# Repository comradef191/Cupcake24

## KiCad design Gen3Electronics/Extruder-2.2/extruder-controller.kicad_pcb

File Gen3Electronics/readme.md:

# About
The electronics within the final Cupcake24 build will be a modernised variant of the original Gen3 electronics, with the following changes made from the original files:

- PCB & Schematics ported to KiCAD 8.0
  - Reorganisation of Schematic to fit into one small page
  - Symbol locations adjusted to make values easier to read
  - Where possible, Schematic symbols swapped for KiCAD equivalents
  - Where possible, PCB footprints swapped for KiCAD equivalents
- PCB outline re-drawn and rounded-off
- PCB modified to run ground through the groundplane, rather than individual traces
- All traces, text, vias ect adjusted to be entirely metric (I.E: 0.3048mm traces (12mill) changed to 0.3mm traces)
- Silkscreen entirely overhauled, with information more clearly marked, text relocated & re-sized for improved readability, and information about Cupcake24 in an out-of-sight place (Generally, the rear of the PCB, or under a large component such as the SD reader)
- Some minor fixes to some traces not being run entirely in straight lines

# Electronics Status:

**RepRap Motherboard v1.2**
- [x] Converted to modern Eagle
- [x] Files Ported to KiCAD 8.0
- [x] Schematic modernised & cleaned-up
- [ ] PCB Modernised & cleaned-up
- [ ] Component sources designated; BoM Complete
- [ ] PCB Ordered
- [ ] PCB Assembled & Tested
- Comment: PCB mostly complete, some cleanup and tweaks to be done.

**Stepper Motor Driver v2.3**
- [x] Converted to modern Eagle
- [x] Files Ported to KiCAD 8.0
- [x] Schematic modernised & cleaned-up
- [x] PCB Modernised & cleaned-up
- [x] Component sources designated; BoM Complete
- [ ] PCB Ordered
- [ ] PCB Assembled & Tested

**Extruder Controller v2.2**
- [x] Converted to modern Eagle
- [x] Files Ported to KiCAD 8.0
- [ ] Schematic modernised & cleaned-up
- [ ] PCB Modernised & cleaned-up
- [ ] Component sources designated; BoM Complete
- [ ] PCB Ordered
- [ ] PCB Assembled & Tested

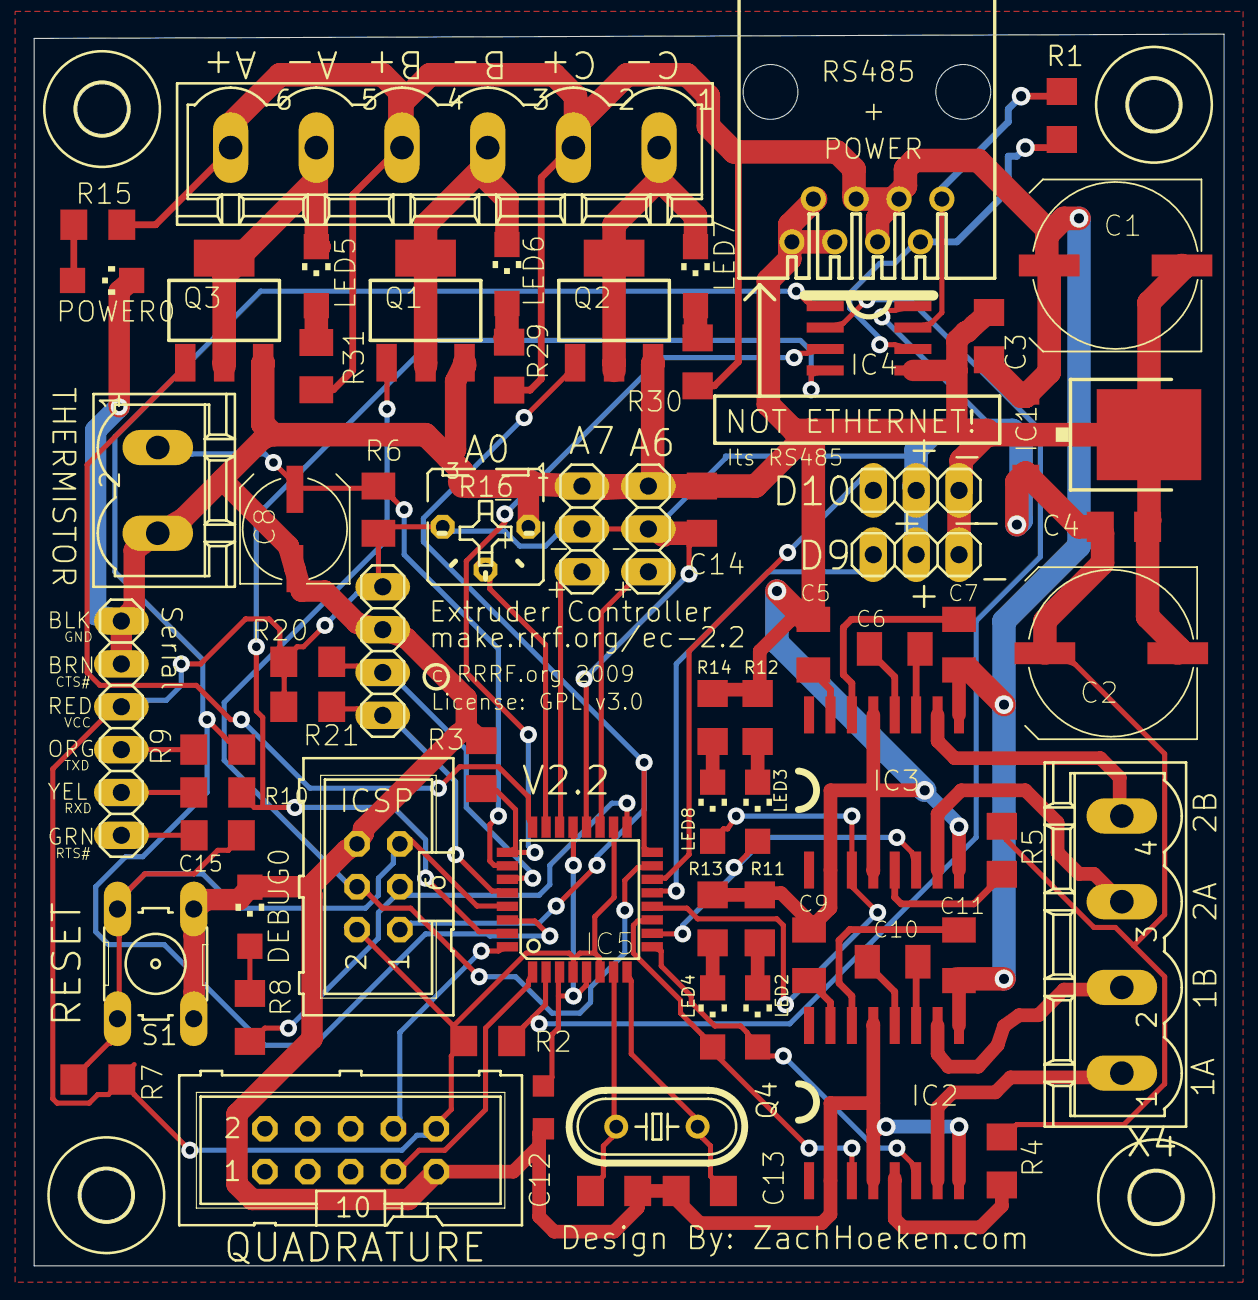
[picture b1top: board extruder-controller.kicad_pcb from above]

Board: 2 copper layers, 70.5 x 73.0 mm, 71 parts (0 on the bottom side), 61 nets.

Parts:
C1, C2: 100uF; UD-10X10_NICHICON
C3, C4, C14, C15: 100nF; C1206
C5, C9: .22uF; C1206K
C6, C7, C10, C11: 100nF; C1206K
C8: 10uF; UD-6,3X5,8_NICHICON
C12, C13: 16pf; C1206
DEBUG0: CHIPLED_1206
H1, H2, H3, H4: MOUNT-HOLE3.0; 3,0
IC1: 7805DT; TO252
IC2, IC3: A3949; SO16W
IC4: SN75176ASOIC; SO08
IC5: ATMEGA168; TQFP32-08
J1: 520426-4
JP2, JP3, JP6, JP7: 1X03
JP4: 1X04
JP5: 1X06
LED2: 1; CHIPLED_1206
LED3: 2; CHIPLED_1206
LED4, LED5, LED6, LED7, LED8: CHIPLED_1206
POWER0: CHIPLED_1206
Q1, Q2, Q3: NIF5002; SOT223
Q4: 16MHZ; HC49_S
R1: 180; R1206
R2, R3: 4.7k; R1206
R4, R5, R7: 10K; R1206
R6: 4.7K; M1206
R8, R9, R10, R11, R12, R13, R14, R15, R29, R30: 1K; R1206
R16: B25P
R20, R21: 4.7K; R1206
R31: 1K; M1206
S1: B3F-10XX
SV1: ML6
SV2: ML10
X1: MSTBV6
X3: MSTBV2
X4: MSTBV4

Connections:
+12V: C1.+, C3.1, C7.2, C11.2, IC1.1, IC2.9, IC3.9, J1.3, J1.4, J1.5, R15.2, R29.2, R30.2, R31.2, X1.2, X1.4, X1.6
A0: IC5.23, R16.S
A1: IC5.24, Q3.1
A2: IC4.3, IC5.25, R3.1
A3: C8.+, IC5.26, R6.1, X3.1
A6: IC5.19, JP6.3
A7: IC5.22, JP7.3
D2: IC5.32, SV2.8
D3: IC5.1, SV2.7
D4: IC4.2, IC5.2, R2.1
D5: IC2.6, IC5.9, LED2.A
D6: IC3.6, IC5.10, LED3.A
D7: IC2.3, IC5.11, LED4.A
D8: IC3.3, IC5.12, LED8.A
D9: IC5.13, JP3.3
D10: IC5.14, JP2.3
D11: IC5.15, Q1.1, SV1.4
D12: IC5.16, Q2.1, SV1.1
D13: IC5.17, R8.2, SV1.3
GND: C1.-, C2.-, C3.2, C4.2, C5.1, C8.-, C9.1, C12.1, C13.1, C14.1, DEBUG0.C, IC1.3, IC2.2, IC2.4, IC2.8, IC2.13, IC3.2, IC3.4, IC3.8, IC3.13, IC4.5, J1.6, J1.7, J1.8, JP2.1, JP3.1, JP4.2, JP5.1, JP5.2, JP6.1, JP7.1, POWER0.C, Q1.3, Q2.3, Q3.3, R3.2, R11.2, R12.2, R13.1, R14.1, R16.A, S1.3, S1.4, SV1.6, SV2.9, X3.2
GNDA: IC5.3, IC5.5, IC5.21
unnamed: IC4.7, J1.1, R1.2
unnamed: IC4.6, J1.2, R1.1
unnamed: C9.2, IC2.15
unnamed: IC2.7, X4.1
unnamed: IC2.10, X4.2
unnamed: C10.2, IC2.12
unnamed: C10.1, IC2.11
unnamed: DEBUG0.A, R8.1
unnamed: C11.1, IC2.14
unnamed: IC3.7, X4.3
unnamed: C5.2, IC3.15
unnamed: IC2.5, R4.2
unnamed: C6.2, IC3.12
unnamed: C6.1, IC3.11
unnamed: C7.1, IC3.14
unnamed: IC3.5, R5.2
unnamed: IC3.10, X4.4
unnamed: LED2.C, R11.1
unnamed: LED3.C, R12.1
unnamed: C14.2, IC5.20
unnamed: JP5.5, R10.1
unnamed: JP5.4, R9.1
unnamed: LED4.C, R13.2
unnamed: LED8.C, R14.2
unnamed: POWER0.A, R15.1
unnamed: C12.2, IC5.7, Q4.2
unnamed: C13.2, IC5.8, Q4.1
unnamed: LED7.C, Q2.2, Q2.4, X1.1
unnamed: LED6.C, Q1.2, Q1.4, X1.3
unnamed: LED5.C, Q3.2, Q3.4, X1.5
unnamed: LED5.A, R31.1
unnamed: LED6.A, R29.1
unnamed: LED7.A, R30.1
RESET: C15.1, IC5.29, R7.1, S1.1, S1.2, SV1.5
RTS#: C15.2, JP5.6
RX: IC4.1, IC5.30, R9.2
SCL: IC5.28, JP4.4, R21.1
SDA: IC5.27, JP4.3, R20.1
TX: IC4.4, IC5.31, R10.2
VCC: C2.+, C4.1, IC1.2, IC4.8, IC5.4, IC5.6, IC5.18, JP2.2, JP3.2, JP4.1, JP5.3, JP6.2, JP7.2, R2.2, R4.1, R5.1, R6.2, R7.2, R16.E, R20.2, R21.2, SV1.2, SV2.10

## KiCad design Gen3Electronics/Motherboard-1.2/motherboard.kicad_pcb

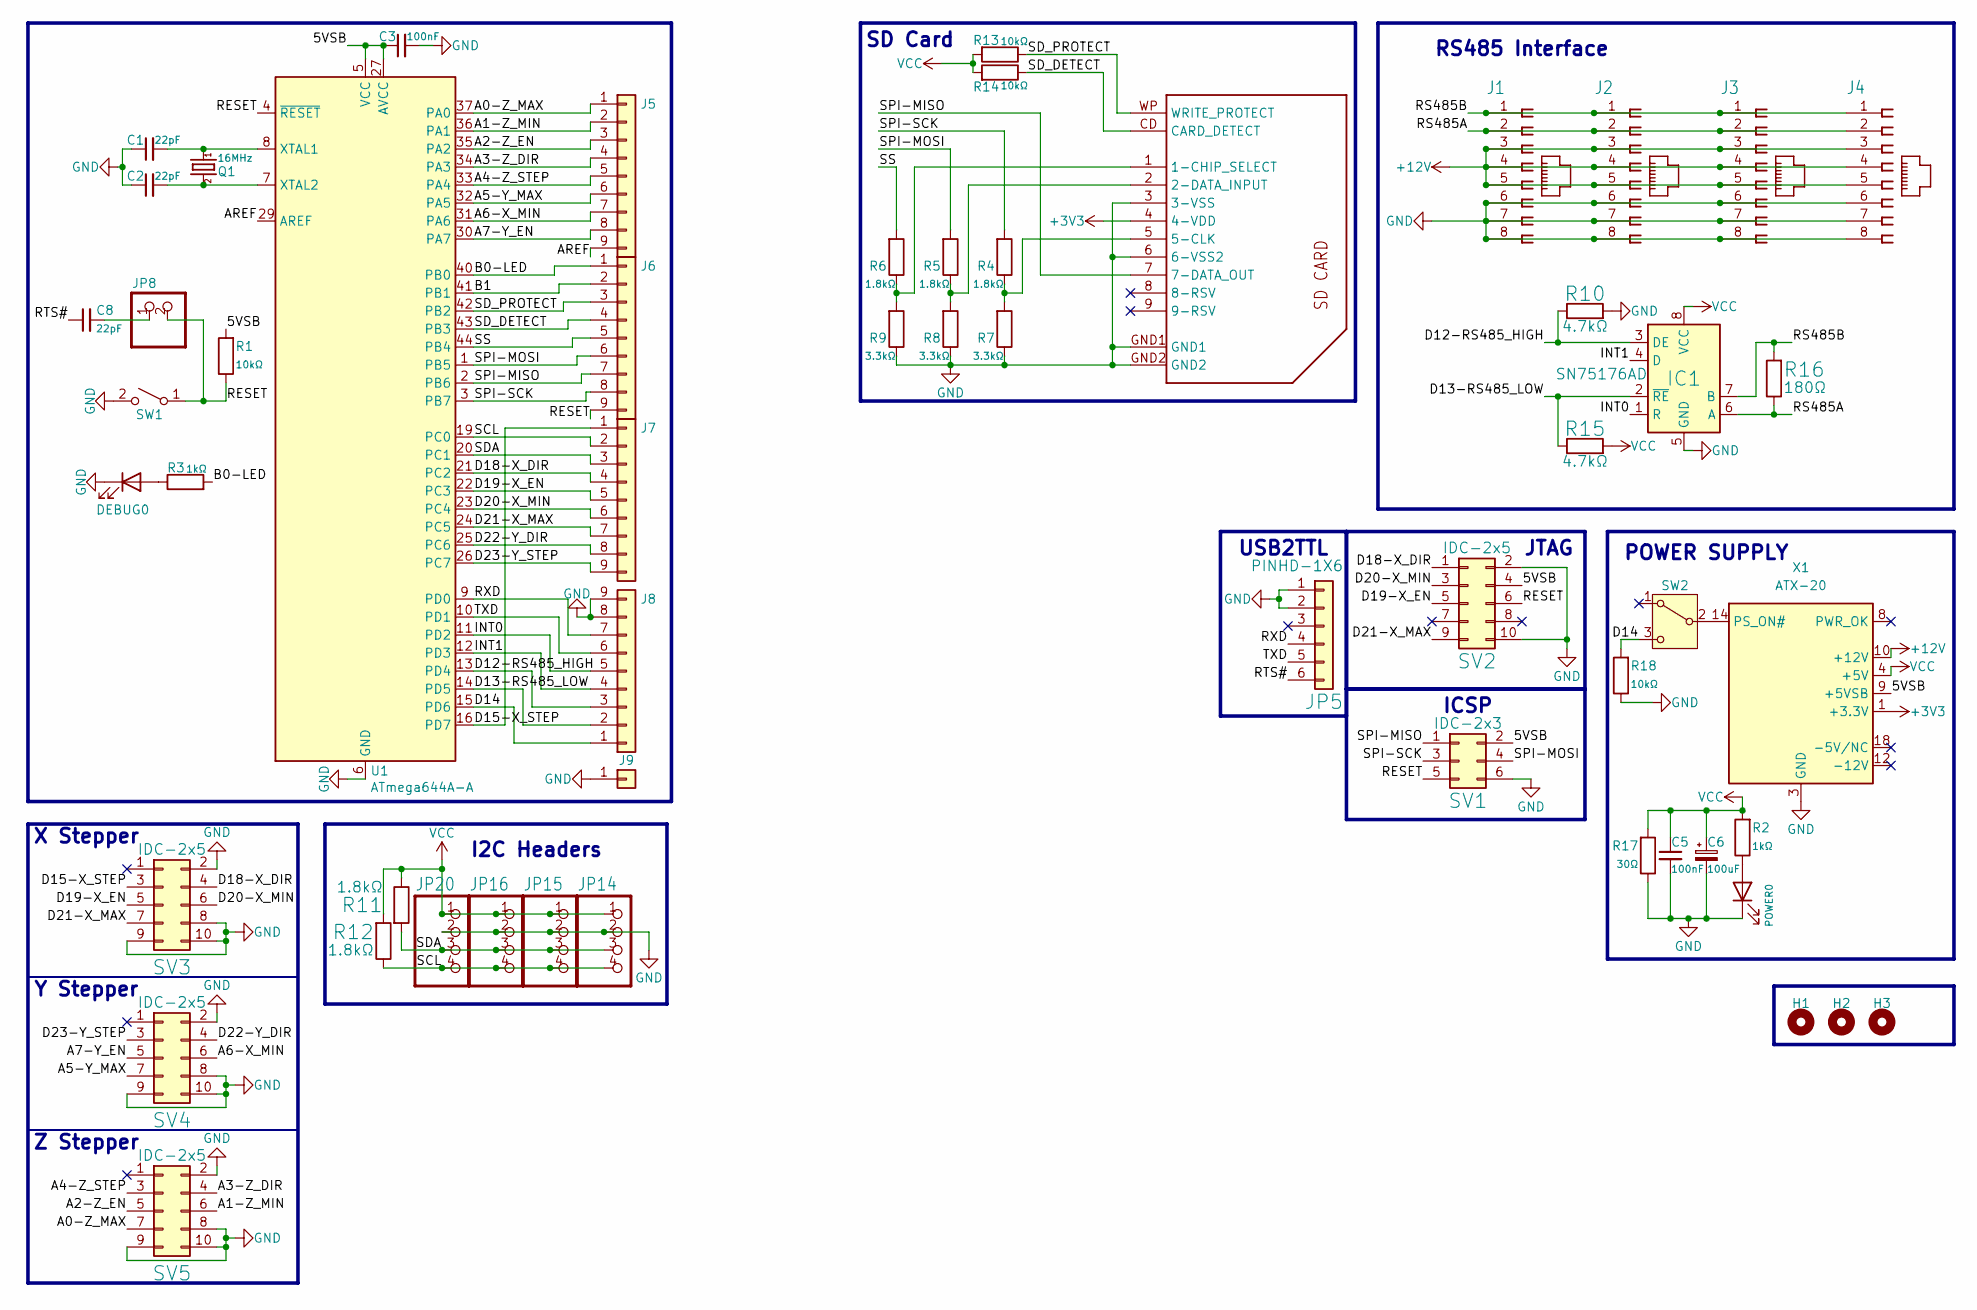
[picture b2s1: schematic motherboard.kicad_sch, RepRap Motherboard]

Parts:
C1, C2, C8: 22pF; C_1206_3216Metric_Pad1.33x1.80mm_HandSolder
C3, C5: 100nF; C_1206_3216Metric_Pad1.33x1.80mm_HandSolder
C6: 100uF; CP_Radial_D8.0mm_P3.50mm; LCSC C2749
DEBUG0: LEDCHIPLED_1206; LED_1206_3216Metric
H1, H2, H3: M3 Mounting Hole; M3 Mounting Hole ~ Classic
IC1: SN75176AD; SOIC-8_3.9x4.9mm_P1.27mm
J1, J2, J3, J4: 555164-1
J5, J6, J7, J8: Conn_01x09; PinSocket_1x09_P2.54mm_Vertical
J9: Conn_01x01; PinSocket_1x01_P2.54mm_Vertical
JP5: PINHD-1X6; 1X06
JP8: PINHD-1X2; 1X02
JP14, JP15, JP16, JP20: PINHD-1X4; 1X04
POWER0: LEDCHIPLED_1206; LED_1206_3216Metric
Q1: 16MHz; Crystal_HC49-U_Vertical
R1, R13, R14, R18: 10kΩ; R_1206_3216Metric_Pad1.30x1.75mm_HandSolder
R2, R3: 1kΩ; R_1206_3216Metric_Pad1.30x1.75mm_HandSolder
R4, R5, R6, R11, R12: 1.8kΩ; R_1206_3216Metric_Pad1.30x1.75mm_HandSolder
R7, R8, R9: 3.3kΩ; R_1206_3216Metric_Pad1.30x1.75mm_HandSolder
R10, R15: 4.7kΩ; R_1206_3216Metric_Pad1.30x1.75mm_HandSolder
R16: 180Ω; R_1206_3216Metric_Pad1.30x1.75mm_HandSolder
R17: 30Ω; R_Axial_Power_L20.0mm_W6.4mm_P22.40mm; LCSC C334301
SV1: IDC-2x3; IDC-Header_2x03_P2.54mm_Vertical
SV2, SV3, SV4, SV5: IDC-2x5; IDC-Header_2x05_P2.54mm_Vertical
SW1: SW_SPST; SW_PUSH_6mm_H5mm; LCSC C5340135
SW2: SW_SPDT; SW-TH_SHOU-HAN_SS12D10G4
U1: ATmega644A-A; TQFP-44_10x10mm_P0.8mm; LCSC C38349
U$8: SDCARD; 3M-SDCARD
X1: ATX-20; Molex_Mini-Fit_Jr_5566-20A2_2x10_P4.20mm_Vertical

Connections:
+3V3: U$8.4 (4-VDD), X1.1 (+3.3V), X1.2 (+3.3V), X1.11 (+3.3V)
+12V: J1.3, J1.4, J1.5, J2.3, J2.4, J2.5, J3.3, J3.4, J3.5, J4.3, J4.4, J4.5, X1.10 (+12V)
/5VSB: C3.1, R1.2, SV1.2, SV2.4, U1.5 (VCC), U1.17 (VCC), U1.27 (AVCC), U1.38 (VCC), X1.9 (+5VSB)
/A0-Z_MAX: J5.1, SV5.7, U1.37 (PA0)
/A1-Z_MIN: J5.2, SV5.6, U1.36 (PA1)
/A2-Z_EN: J5.3, SV5.5, U1.35 (PA2)
/A3-Z_DIR: J5.4, SV5.4, U1.34 (PA3)
/A4-Z_STEP: J5.5, SV5.3, U1.33 (PA4)
/A5-Y_MAX: J5.6, SV4.7, U1.32 (PA5)
/A6-X_MIN: J5.7, SV4.6, U1.31 (PA6)
/A7-Y_EN: J5.8, SV4.5, U1.30 (PA7)
/AREF: J5.9, U1.29 (AREF)
/B0-LED: J6.1, R3.2, U1.40 (PB0)
/B1: J6.2, U1.41 (PB1)
/D12-RS485_HIGH: IC1.3 (DE), J8.3, R10.1, U1.13 (PD4)
/D13-RS485_LOW: IC1.2 (~RE), J8.2, R15.1, U1.14 (PD5)
/D14: J8.1, R18.2, SW2.3 (C), U1.15 (PD6)
/D15-X_STEP: J7.1, SV3.3, U1.16 (PD7)
/D18-X_DIR: J7.4, SV2.1, SV3.4, U1.21 (PC2)
/D19-X_EN: J7.5, SV2.5, SV3.5, U1.22 (PC3)
/D20-X_MIN: J7.6, SV2.3, SV3.6, U1.23 (PC4)
/D21-X_MAX: J7.7, SV2.9, SV3.7, U1.24 (PC5)
/D22-Y_DIR: J7.8, SV4.4, U1.25 (PC6)
/D23-Y_STEP: J7.9, SV4.3, U1.26 (PC7)
/INT0: IC1.1 (R), J8.5, U1.11 (PD2)
/INT1: IC1.4 (D), J8.4, U1.12 (PD3)
/RESET: J6.9, JP8.2, R1.1, SV1.5, SV2.6, SW1.1 (A), U1.4 (~RESET)
/RS485A: IC1.6 (A), J1.2, J2.2, J3.2, J4.2, R16.1
/RS485B: IC1.7 (B), J1.1, J2.1, J3.1, J4.1, R16.2
/RTS#: C8.1, JP5.6
/RXD: J8.7, JP5.4, U1.9 (PD0)
/SCL: J7.2, JP14.4, JP15.4, JP16.4, JP20.4, R12.1, U1.19 (PC0)
/SDA: J7.3, JP14.3, JP15.3, JP16.3, JP20.3, R11.2, U1.20 (PC1)
/SD_DETECT: J6.4, R14.1, U1.43 (PB3), U$8.CD (CARD_DETECT)
/SD_PROTECT: J6.3, R13.1, U1.42 (PB2), U$8.WP (WRITE_PROTECT)
/SPI-MISO: J6.7, SV1.1, U1.2 (PB6), U$8.7 (7-DATA_OUT)
/SPI-MOSI: J6.6, R5.2, SV1.4, U1.1 (PB5)
/SPI-SCK: J6.8, R4.2, SV1.3, U1.3 (PB7)
/SS: J6.5, R6.2, U1.44 (PB4)
/TXD: J8.6, JP5.5, U1.10 (PD1)
GND: C1.1, C2.1, C3.2, C5.2, C6.2, DEBUG0.1 (K), IC1.5 (GND), J1.6, J1.7, J1.8, J2.6, J2.7, J2.8, J3.6, J3.7, J3.8, J4.6, J4.7, J4.8, J8.8, J8.9, J9.1, JP5.1, JP5.2, JP14.2, JP15.2, JP16.2, JP20.2, POWER0.1 (K), R7.1, R8.1, R9.1, R10.2, R17.1, R18.1, SV1.6, SV2.2, SV2.10, SV3.2, SV3.8, SV3.9, SV3.10, SV4.2, SV4.8, SV4.9, SV4.10, SV5.2, SV5.8, SV5.9, SV5.10, SW1.2 (B), U1.6 (GND), U1.18 (GND), U1.28 (GND), U1.39 (GND), U$8.3 (3-VSS), U$8.6 (6-VSS2), U$8.GND1, U$8.GND2, X1.3 (GND), X1.5 (GND), X1.7 (GND), X1.13 (GND), X1.15 (GND), X1.16 (GND), X1.17 (GND)
unnamed: C8.2, JP8.1
unnamed: DEBUG0.2 (A), R3.1
unnamed: POWER0.2 (A), R2.1
unnamed: SW2.2 (B), X1.14 (PS_ON#)
unnamed: C1.2, Q1.1, U1.8 (XTAL1)
unnamed: C2.2, Q1.2, U1.7 (XTAL2)
unnamed: R6.1, R9.2, U$8.1 (1-CHIP_SELECT)
unnamed: R5.1, R8.2, U$8.2 (2-DATA_INPUT)
unnamed: R4.1, R7.2, U$8.5 (5-CLK)
VCC: C5.1, C6.1, IC1.8 (VCC), JP14.1, JP15.1, JP16.1, JP20.1, R2.2, R11.1, R12.2, R13.2, R14.2, R15.2, R17.2, X1.4 (+5V), X1.6 (+5V), X1.19 (+5V), X1.20 (+5V)

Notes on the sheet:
Z Stepper
USB2TTL
SD Card
JTAG
RS485 Interface
Y Stepper
ICSP
X Stepper
POWER SUPPLY
I2C Headers

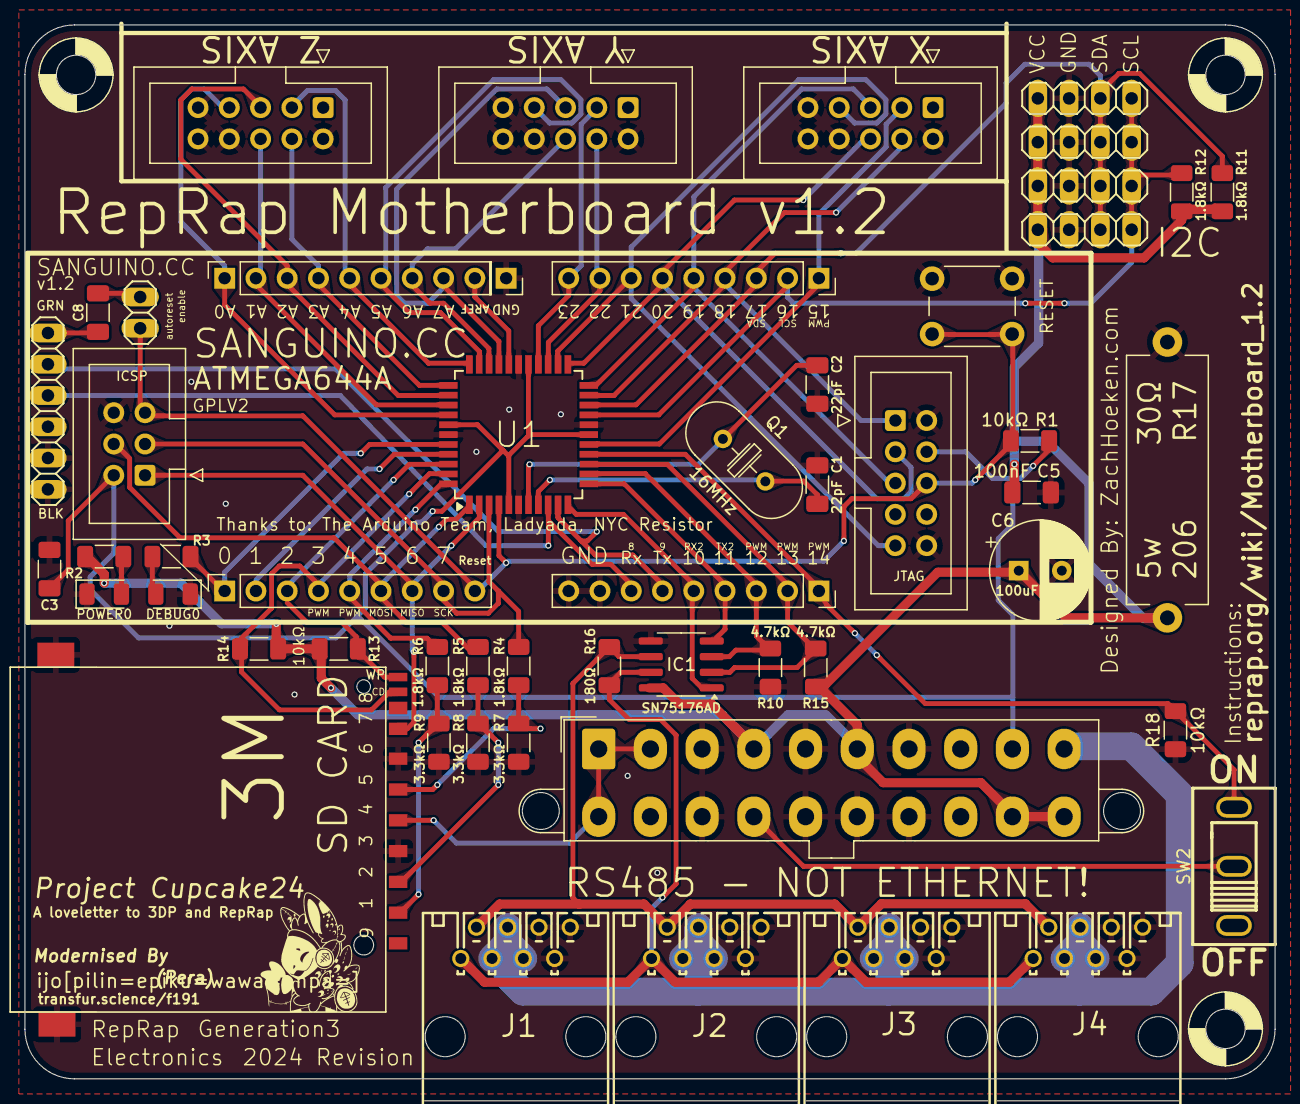
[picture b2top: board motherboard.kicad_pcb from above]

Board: 2 copper layers, 101.5 x 85.6 mm, 56 parts (0 on the bottom side), 51 nets.

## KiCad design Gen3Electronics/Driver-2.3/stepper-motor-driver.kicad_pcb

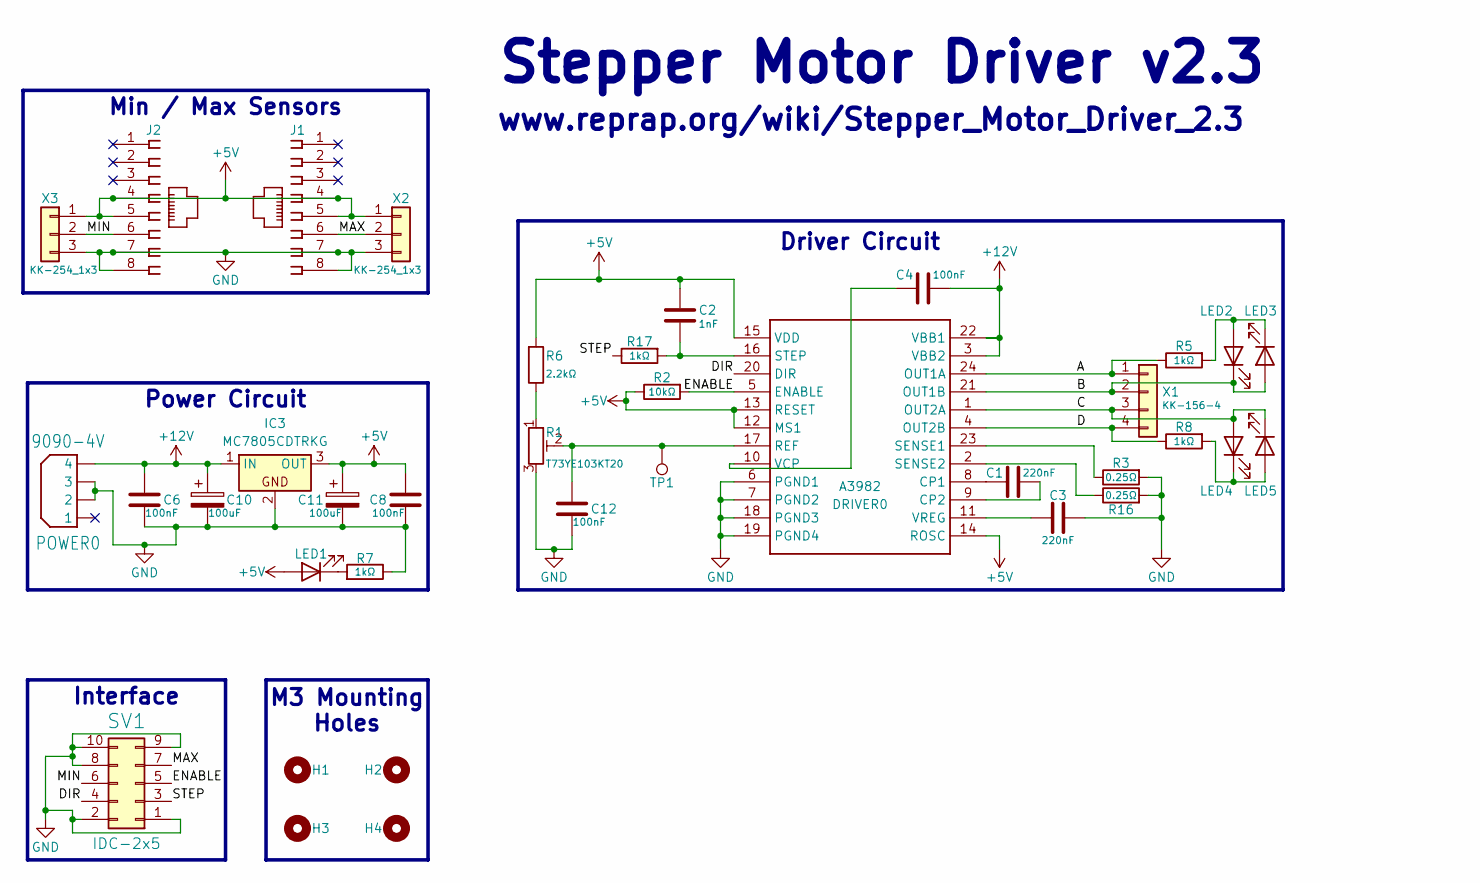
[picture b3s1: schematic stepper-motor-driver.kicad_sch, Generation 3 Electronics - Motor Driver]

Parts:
C1, C3: 220nF; C_1206_3216Metric_Pad1.33x1.80mm_HandSolder; LCSC C377090
C2: 1nF; C_1206_3216Metric_Pad1.33x1.80mm_HandSolder; LCSC C5448899
C4, C6, C8, C12: 100nF; C_1206_3216Metric_Pad1.33x1.80mm_HandSolder; LCSC C841554
C10, C11: 100uF; CP_Elec_10x10; LCSC C250828
DRIVER0: A3982; SOIC-24W_7.5x15.4mm_P1.27mm
H1, H2, H3, H4: MountingHole; M3 Mounting Hole ~ Classic
IC3: MC7805CDTRKG; TO-252-2; LCSC C54285
J1, J2: 520426-4; LCSC C3000202
LED1, LED2, LED3: GREEN; LED_1206_3216Metric_Pad1.42x1.75mm_HandSolder; LCSC C2980185
LED4, LED5: RED; LED_1206_3216Metric_Pad1.42x1.75mm_HandSolder; LCSC C2892757
POWER0: 9090-4V; LCSC C492551
R1: T73YE103KT20; Potentiometer_Vishay_T73YP_Vertical; LCSC C58159
R2: 10kΩ; R_1206_3216Metric_Pad1.30x1.75mm_HandSolder; LCSC C2907423
R3, R16: 0.25Ω; R_2512_6332Metric_Pad1.52x3.35mm_HandSolder; LCSC C25467
R5, R7, R8, R17: 1kΩ; R_1206_3216Metric_Pad1.30x1.75mm_HandSolder; LCSC C2907440
R6: 2.2kΩ; R_1206_3216Metric_Pad1.30x1.75mm_HandSolder; LCSC C26038
SV1: IDC-2x5; IDC-Header_2x05_P2.54mm_Vertical; LCSC C429962
TP1: TestPoint; P1-13
X1: KK-156-4; LCSC C10379
X2, X3: KK-254_1x3; Molex_KK-254_AE-6410-03A_1x03_P2.54mm_Vertical

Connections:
+5V: C2.2, C8.2, C11.1, DRIVER0.12 (MS1), DRIVER0.13 (RESET), DRIVER0.14 (ROSC), DRIVER0.15 (VDD), IC3.3 (OUT), J1.4, J1.5, J2.4, J2.5, LED1.2 (A), R2.1, R6.2, X2.1, X3.1
+12V: C4.2, C6.2, C10.1, DRIVER0.3 (VBB2), DRIVER0.22 (VBB1), IC3.1 (IN), POWER0.4
/A: DRIVER0.24 (OUT1A), R5.1, X1.1
/B: DRIVER0.21 (OUT1B), LED2.1 (K), LED3.2 (A), X1.2
/C: DRIVER0.1 (OUT2A), LED4.2 (A), LED5.1 (K), X1.3
/D: DRIVER0.4 (OUT2B), R8.1, X1.4
/DIR: DRIVER0.20 (DIR), SV1.4
/ENABLE: DRIVER0.5 (ENABLE), R2.2, SV1.5
/MAX: J1.6, SV1.7, X2.2
/MIN: J2.6, SV1.6, X3.2
/STEP: R17.1, SV1.3
GND: C3.2, C6.1, C8.1, C10.2, C11.2, C12.1, DRIVER0.6 (PGND1), DRIVER0.7 (PGND2), DRIVER0.18 (PGND3), DRIVER0.19 (PGND4), IC3.2, J1.7, J1.8, J2.7, J2.8, POWER0.2, POWER0.3, R1.3, R3.2, R7.1, R16.2, SV1.1, SV1.2, SV1.8, SV1.9, SV1.10, X2.3, X3.3
unnamed: C1.1, DRIVER0.8 (CP1)
unnamed: C1.2, DRIVER0.9 (CP2)
unnamed: C12.2, DRIVER0.17 (REF), R1.2, TP1.1
unnamed: DRIVER0.23 (SENSE1), R3.1
unnamed: DRIVER0.2 (SENSE2), R16.1
unnamed: C2.1, DRIVER0.16 (STEP), R17.2
unnamed: C4.1, DRIVER0.10 (VCP)
unnamed: C3.1, DRIVER0.11 (VREG)
unnamed: LED1.1 (K), R7.2
unnamed: LED2.2 (A), LED3.1 (K), R5.2
unnamed: LED4.1 (K), LED5.2 (A), R8.2
unnamed: R1.1, R6.1

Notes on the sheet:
www.reprap.org/wiki/Stepper_Motor_Driver_2.3
Power Circuit
Interface
Stepper Motor Driver v2.3
M3 Mounting Holes
Min / Max Sensors
Driver Circuit

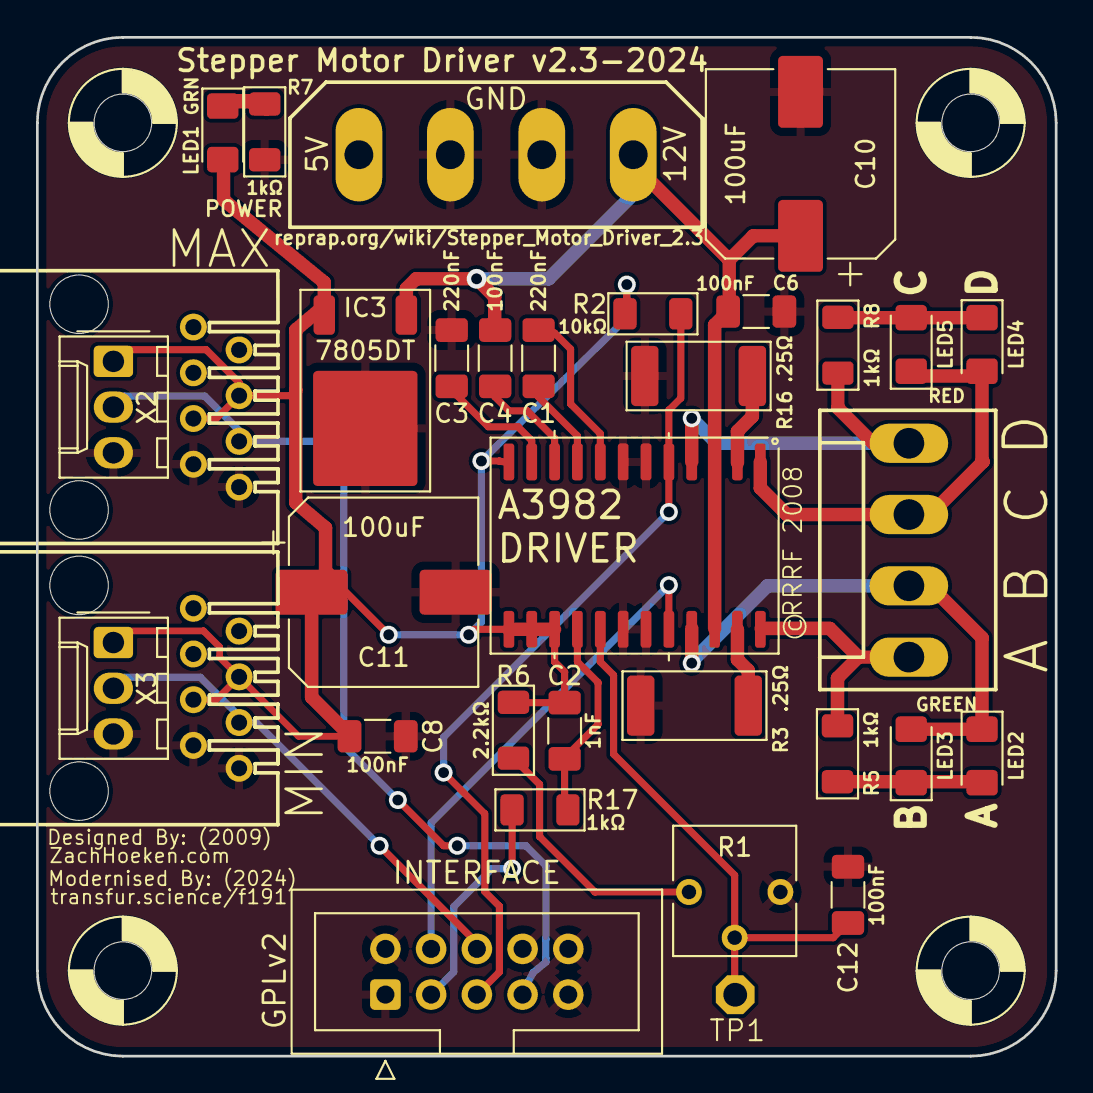
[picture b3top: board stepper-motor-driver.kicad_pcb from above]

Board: 2 copper layers, 56.6 x 56.6 mm, 37 parts (0 on the bottom side), 24 nets.

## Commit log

2024-11-07 Add all current files for the Electronics

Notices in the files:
Gen3Electronics/Driver-2.3/stepper-motor-driver.kicad_pcb:
GPLv2
Gen3Electronics/Extruder-2.2/extruder-controller.kicad_pcb:
License: GPL v3.0
